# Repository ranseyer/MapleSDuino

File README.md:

View this project on [CADLAB.io](https://cadlab.io/project/2431). 

# MapleSDuino
 Signalduino Hardware based on a Maple-Mini

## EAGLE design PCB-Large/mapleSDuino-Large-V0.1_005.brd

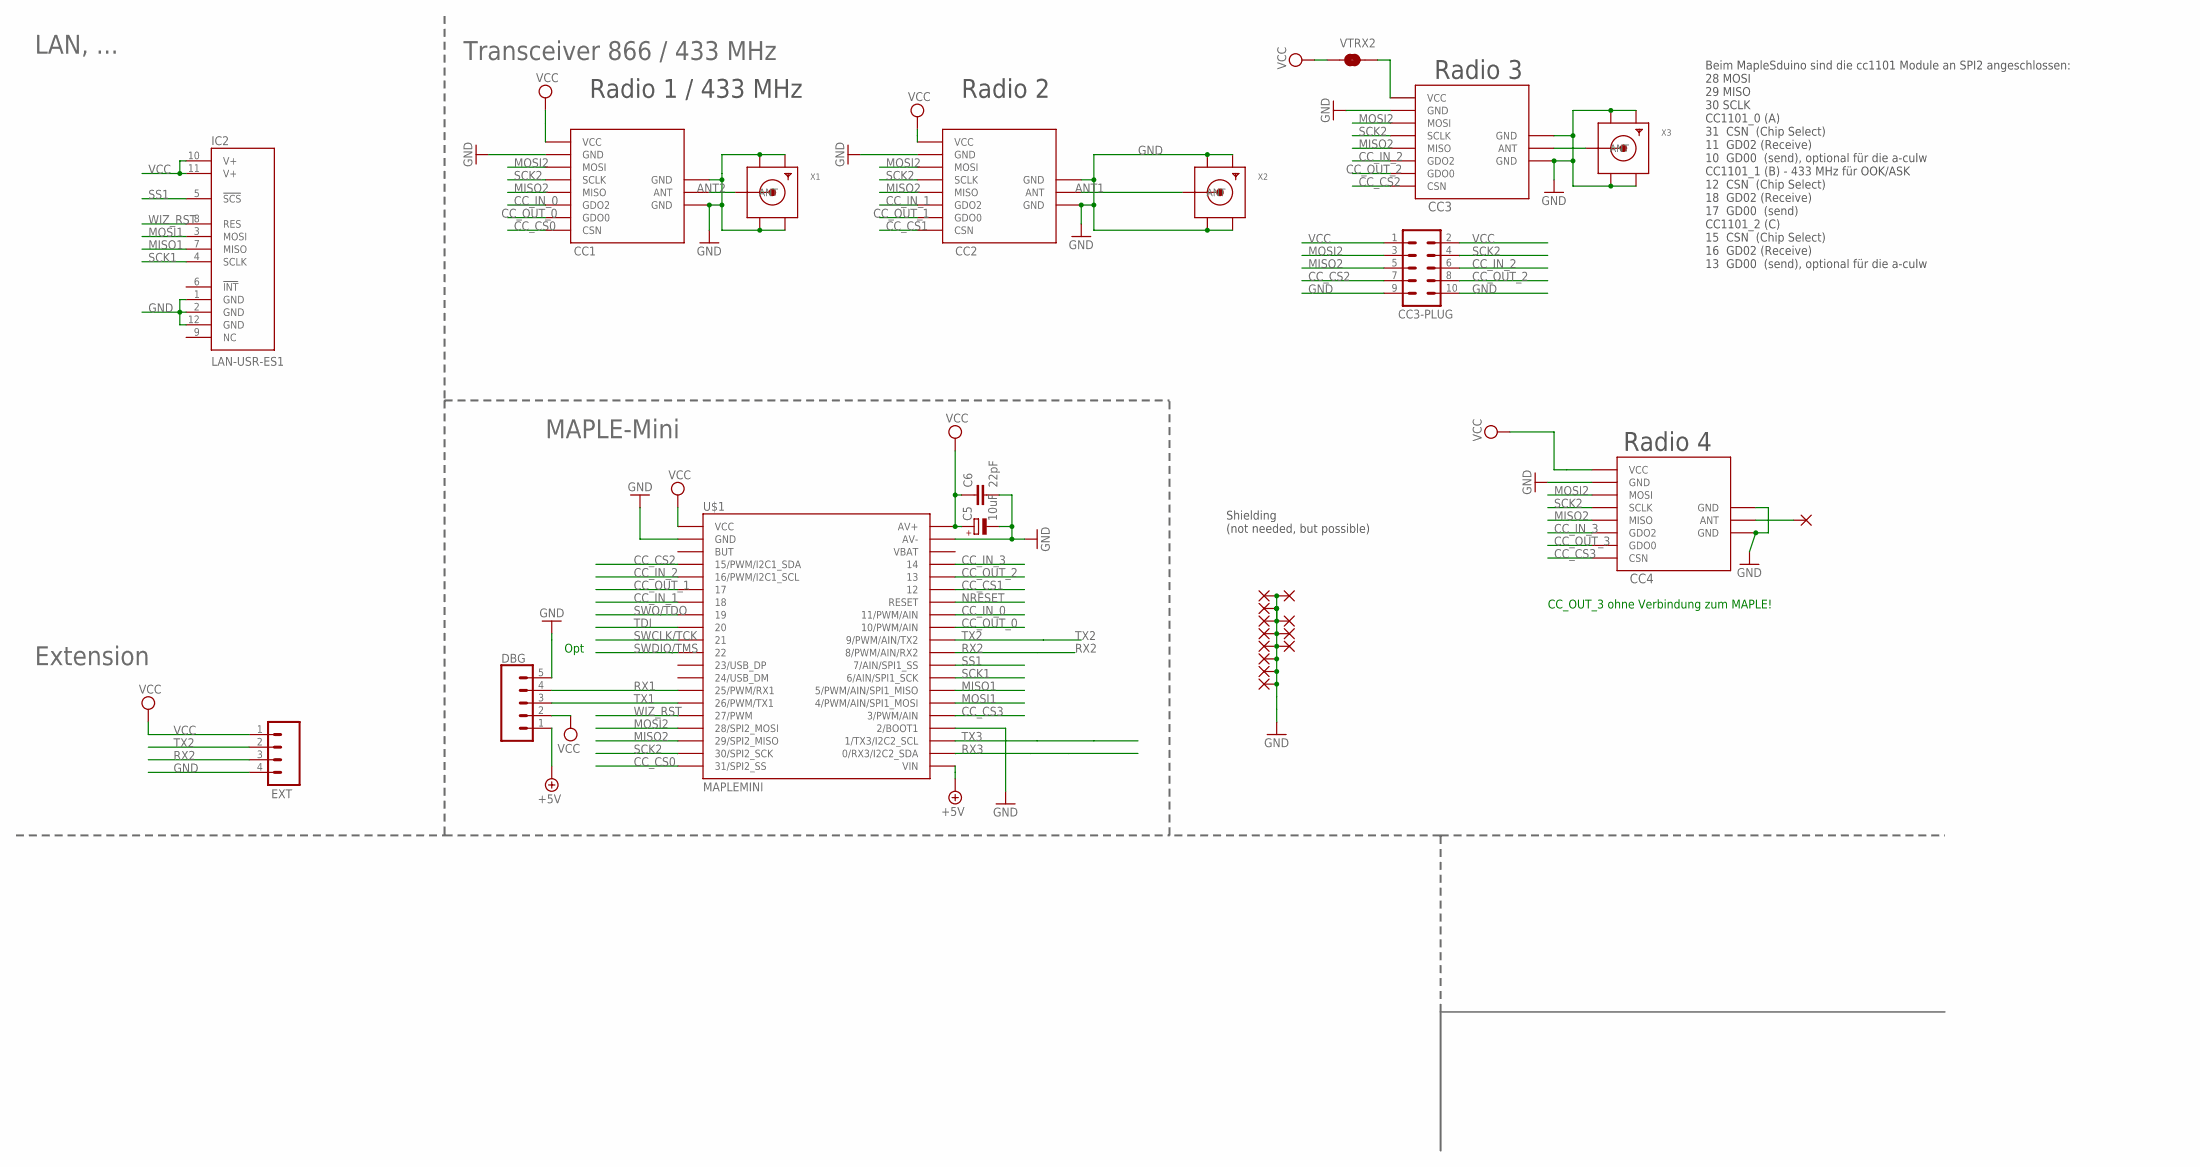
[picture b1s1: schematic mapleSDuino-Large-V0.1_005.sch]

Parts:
C5: 10uF; R/2012-12W
C6: 22pF; C0805
CC1: CC1101; CC1101_MODULE1_SMD
CC2, CC3, CC4: CC1101_MODULE1SMD; CC1101_MODULE1_SMD
CC3-PLUG: MA05-2
DBG: CONN_05LOCK; 1X05_LOCK
EXT: CONN_04PTH; 1X04
IC2: LAN-USR-ES1; USR-ES1
PAD1, PAD2, PAD3, PAD4, PAD5, PAD6, PAD7, PAD8, PAD9, PAD10, PAD11, PAD12, PAD13: WIREPADSMD1,27-254; SMD1,27-2,54
U$1: MAPLEMINI; 20-DIP
VTRX2: JUMPER-SMT_2_NC_TRACE_SILK; SMT-JUMPER_2_NC_TRACE_SILK
X1, X2, X3: SMACONNECTOR_EDGE; SMA_EDGELAUNCH

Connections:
+5V: DBG.1, U$1.21 (VIN)
ANT1: CC2.ANT, X2.P (ANT)
ANT2: CC1.ANT, X1.P (ANT)
ANT3: CC3.ANT, X3.P (ANT)
CC_CS0: CC1.CSN, U$1.20 (31/SPI2_SS)
CC_CS1: CC2.CSN, U$1.35 (12)
CC_CS2: CC3.CSN, CC3-PLUG.7, U$1.4 (15/PWM/I2C1_SDA)
CC_CS3: CC4.CSN, U$1.25 (3/PWM/AIN)
CC_IN_0: CC1.GDO2, U$1.33 (11/PWM/AIN)
CC_IN_1: CC2.GDO2, U$1.7 (18)
CC_IN_2: CC3.GDO2, CC3-PLUG.6, U$1.5 (16/PWM/I2C1_SCL)
CC_IN_3: CC4.GDO2, U$1.37 (14)
CC_OUT_0: CC1.GDO0, U$1.32 (10/PWM/AIN)
CC_OUT_1: CC2.GDO0, U$1.6 (17)
CC_OUT_2: CC3.GDO0, CC3-PLUG.8, U$1.36 (13)
CC_OUT_3: CC4.GDO0
GND: C5.-, C6.2, CC1.GND@0 (GND), CC1.GND@1 (GND), CC1.GND@2 (GND), CC2.GND@0 (GND), CC2.GND@1 (GND), CC2.GND@2 (GND), CC3.GND@0 (GND), CC3.GND@1 (GND), CC3.GND@2 (GND), CC3-PLUG.9, CC3-PLUG.10, CC4.GND@0 (GND), CC4.GND@1 (GND), CC4.GND@2 (GND), DBG.5, EXT.4, IC2.1 (GND), IC2.2 (GND), IC2.12 (GND), PAD1.1, PAD2.1, PAD3.1, PAD4.1, PAD5.1, PAD6.1, PAD7.1, PAD8.1, PAD9.1, PAD10.1, PAD11.1, PAD12.1, U$1.2 (GND), U$1.24 (2/BOOT1), U$1.39 (AV-), X1.GND@1 (GND4), X1.GND@2 (GND3), X1.GND@3 (GND2), X1.GND@4 (GND1), X2.GND@1 (GND4), X2.GND@2 (GND3), X2.GND@3 (GND2), X2.GND@4 (GND1), X3.GND@1 (GND4), X3.GND@2 (GND3), X3.GND@3 (GND2), X3.GND@4 (GND1)
MISO1: IC2.7 (MISO), U$1.27 (5/PWM/AIN/SPI1_MISO)
MISO2: CC1.MISO, CC2.MISO, CC3.MISO, CC3-PLUG.5, CC4.MISO, U$1.18 (29/SPI2_MISO)
MOSI1: IC2.3 (MOSI), U$1.26 (4/PWM/AIN/SPI1_MOSI)
MOSI2: CC1.MOSI, CC2.MOSI, CC3.MOSI, CC3-PLUG.3, CC4.MOSI, U$1.17 (28/SPI2_MOSI)
unnamed: CC3.VCC, VTRX2.2
unnamed: CC4.ANT, PAD13.1
NRESET: U$1.34 (RESET)
RX1: DBG.4, U$1.14 (25/PWM/RX1)
RX2: EXT.3, U$1.30 (8/PWM/AIN/RX2)
RX3: U$1.22 (0/RX3/I2C2_SDA)
SCK1: IC2.4 (SCLK), U$1.28 (6/AIN/SPI1_SCK)
SCK2: CC1.SCLK, CC2.SCLK, CC3.SCLK, CC3-PLUG.4, CC4.SCLK, U$1.19 (30/SPI2_SCK)
SS1: IC2.5 (!SCS!), U$1.29 (7/AIN/SPI1_SS)
SWCLK/TCK: U$1.10 (21)
SWDIO/TMS: U$1.11 (22)
SWO/TDO: U$1.8 (19)
TDI: U$1.9 (20)
TX1: DBG.3, U$1.15 (26/PWM/TX1)
TX2: EXT.2, U$1.31 (9/PWM/AIN/TX2)
TX3: U$1.23 (1/TX3/I2C2_SCL)
VCC: C5.+, C6.1, CC1.VCC, CC2.VCC, CC3-PLUG.1, CC3-PLUG.2, CC4.VCC, DBG.2, EXT.1, IC2.10 (V+), IC2.11 (V+), U$1.1 (VCC), U$1.40 (AV+), VTRX2.1
WIZ_RST: IC2.8 (RES), U$1.16 (27/PWM)

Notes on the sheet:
Radio 2
Radio 1 / 433 MHz
Opt
Extension
MAPLE-Mini
Transceiver 866 / 433 MHz
LAN, ...
Radio 3
Shielding (not needed, but possible)
Radio 4
CC_OUT_3 ohne Verbindung zum MAPLE!
Beim MapleSduino sind die cc1101 Module an SPI2 angeschlossen: 28 MOSI 29 MISO 30 SCLK CC1101_0 (A) 31 CSN (Chip Select) 11 GD02 (Receive) 10 GD00 (send), optional für die a-culw CC1101_1 (B) - 433 MHz für OOK/ASK 12 CSN (Chip Select) 18 GD02 (Receive) 17 GD00 (send) CC1101_2 (C) 15 CSN (Chip Selec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

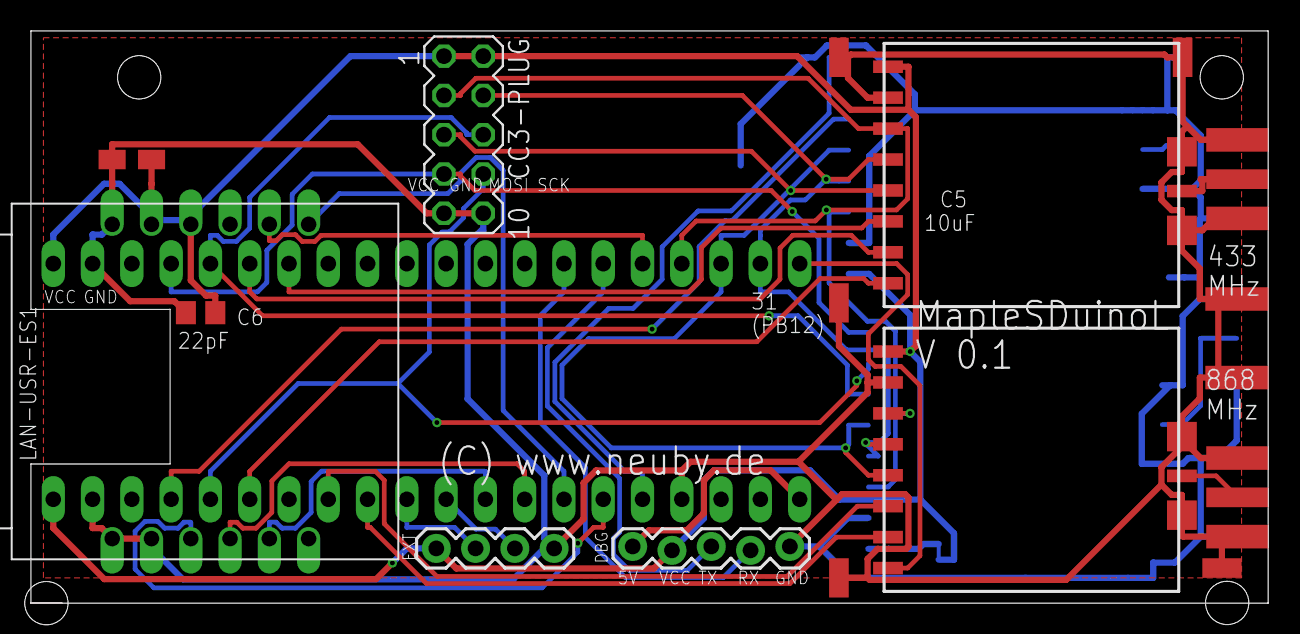
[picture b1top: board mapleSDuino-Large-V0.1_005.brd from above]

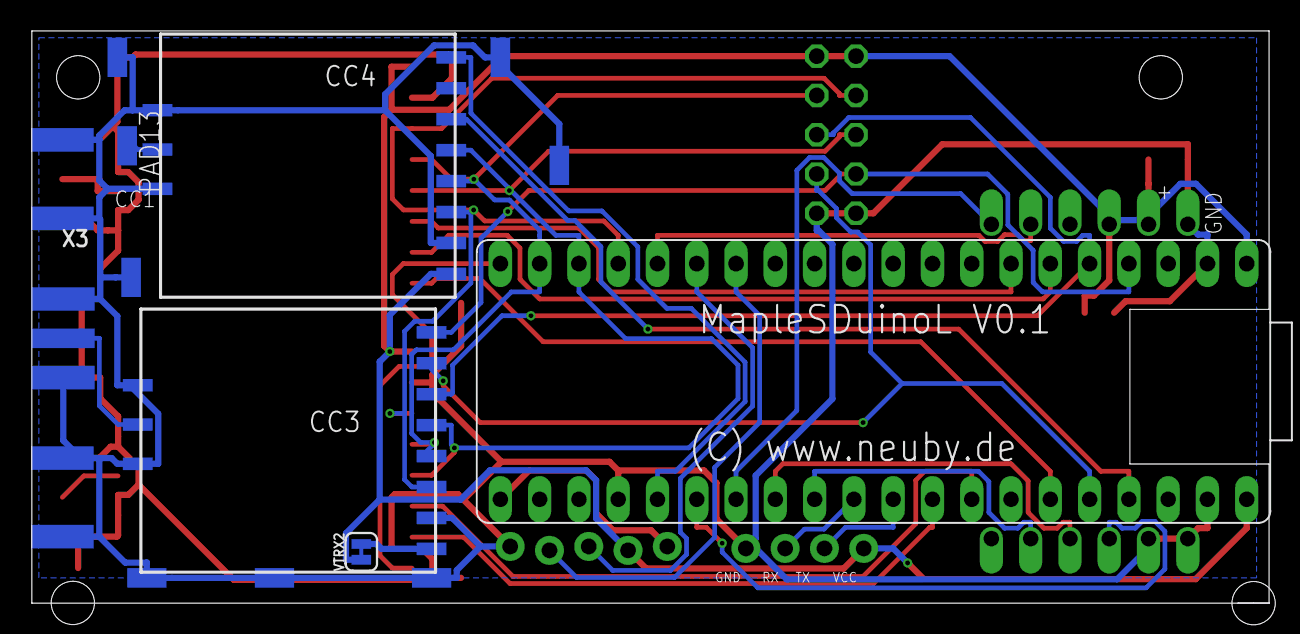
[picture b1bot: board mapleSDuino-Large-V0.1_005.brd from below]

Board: 2 copper layers, 80.0 x 37.0 mm, 28 parts (13 on the bottom side), 31 nets.

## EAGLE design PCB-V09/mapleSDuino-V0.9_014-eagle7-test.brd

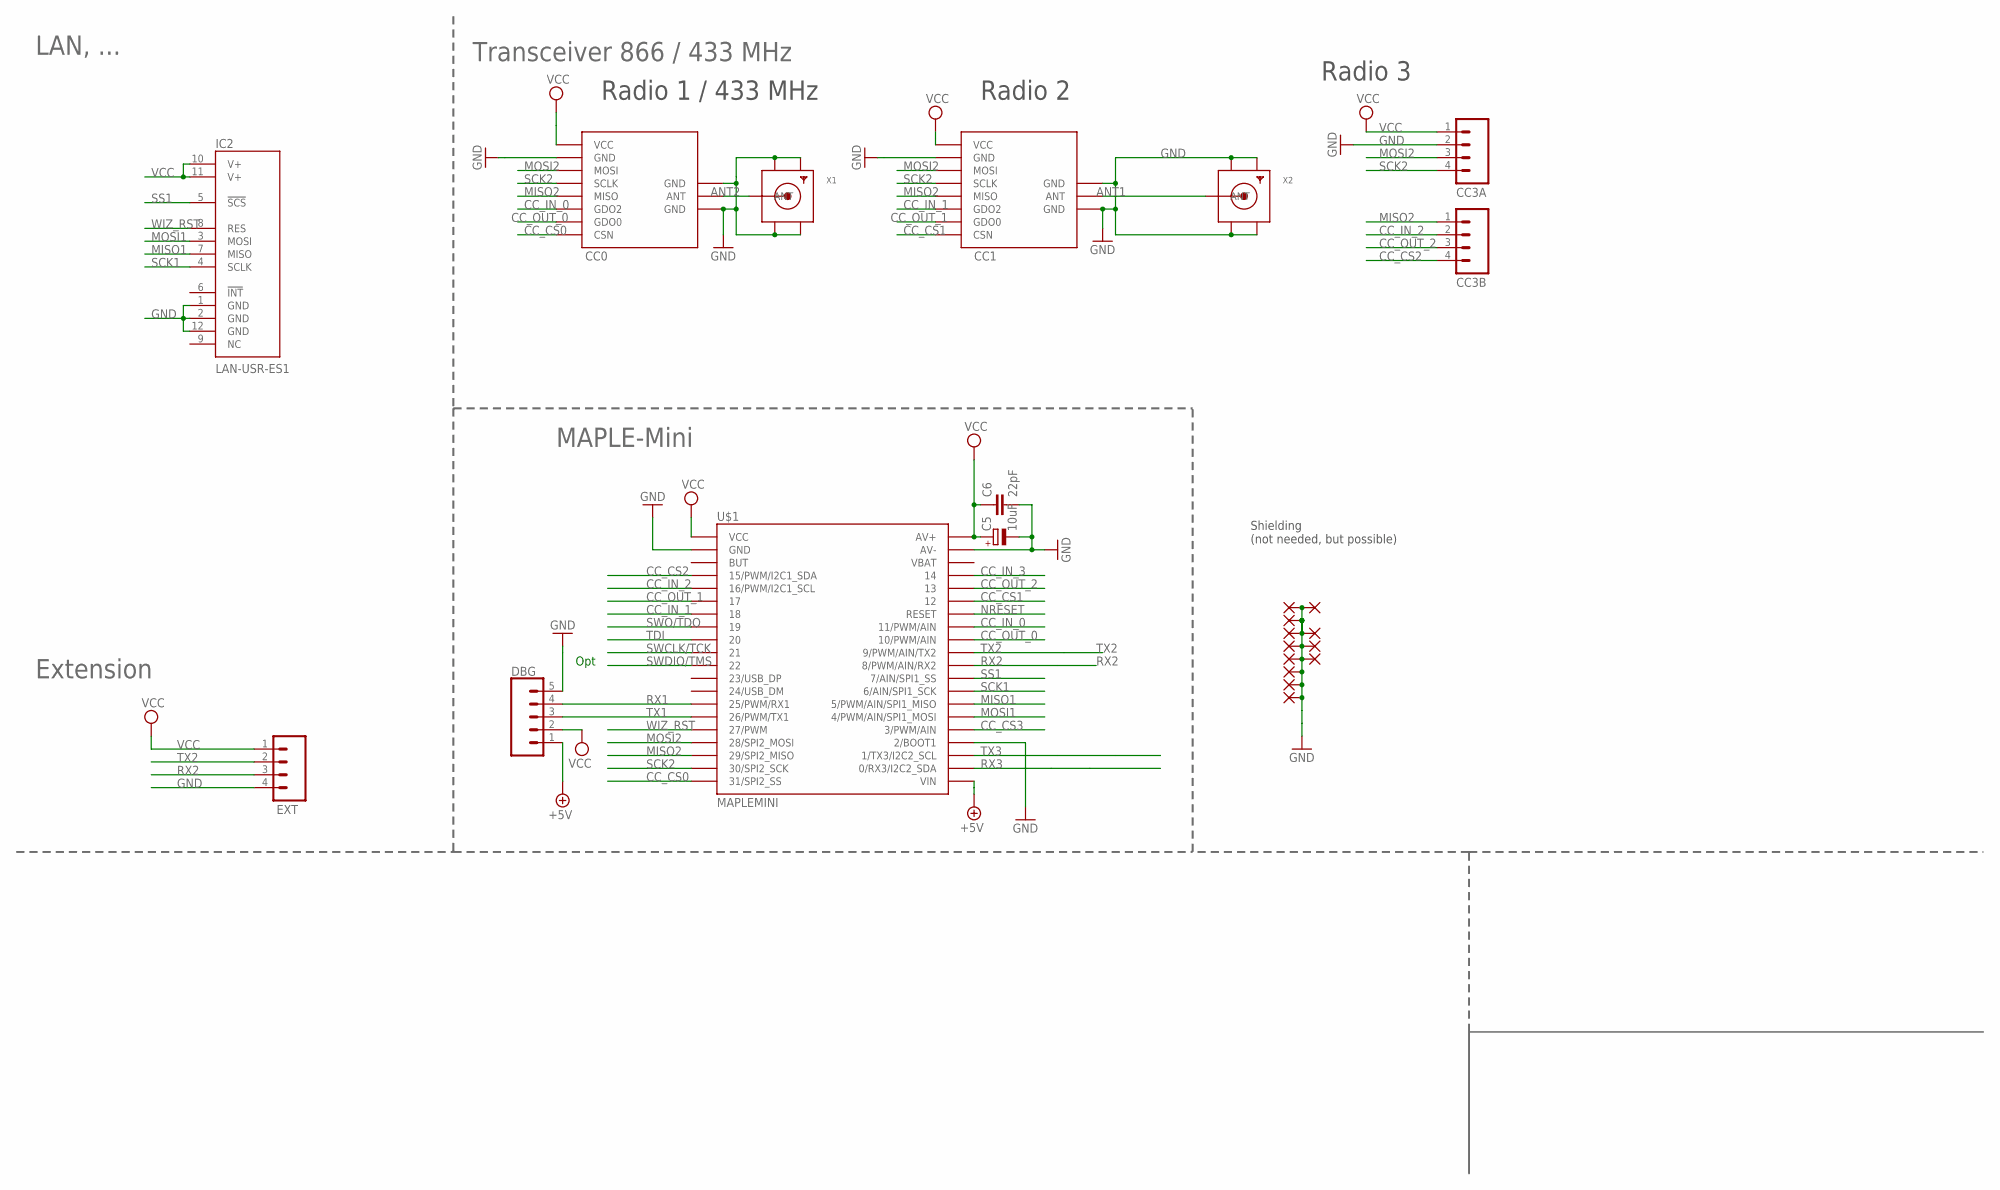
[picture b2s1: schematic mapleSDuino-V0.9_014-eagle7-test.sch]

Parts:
C5: 10uF; R/2012-12W
C6: 22pF; C0805
CC0: CC1101; CC1101_MODULE1_SMD
CC1: CC1101_MODULE1SMD; CC1101_MODULE1_SMD
CC3A, CC3B: CONN_04PTH; 1X04
DBG: CONN_05LOCK; 1X05_LOCK
EXT: CONN_04PTH; 1X04
IC2: LAN-USR-ES1; USR-ES1
PAD1, PAD2, PAD3, PAD4, PAD5, PAD6, PAD7, PAD8, PAD9, PAD10, PAD11, PAD12: WIREPADSMD1,27-254; SMD1,27-2,54
U$1: MAPLEMINI; 20-DIP
X1, X2: SMACONNECTOR_EDGE; SMA_EDGELAUNCH

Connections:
+5V: DBG.1, U$1.21 (VIN)
ANT1: CC1.ANT, X2.P (ANT)
ANT2: CC0.ANT, X1.P (ANT)
CC_CS0: CC0.CSN, U$1.20 (31/SPI2_SS)
CC_CS1: CC1.CSN, U$1.35 (12)
CC_CS2: CC3B.4, U$1.4 (15/PWM/I2C1_SDA)
CC_CS3: U$1.25 (3/PWM/AIN)
CC_IN_0: CC0.GDO2, U$1.33 (11/PWM/AIN)
CC_IN_1: CC1.GDO2, U$1.7 (18)
CC_IN_2: CC3B.2, U$1.5 (16/PWM/I2C1_SCL)
CC_IN_3: U$1.37 (14)
CC_OUT_0: CC0.GDO0, U$1.32 (10/PWM/AIN)
CC_OUT_1: CC1.GDO0, U$1.6 (17)
CC_OUT_2: CC3B.3, U$1.36 (13)
GND: C5.-, C6.2, CC0.GND@0 (GND), CC0.GND@1 (GND), CC0.GND@2 (GND), CC1.GND@0 (GND), CC1.GND@1 (GND), CC1.GND@2 (GND), CC3A.2, DBG.5, EXT.4, IC2.1 (GND), IC2.2 (GND), IC2.12 (GND), PAD1.1, PAD2.1, PAD3.1, PAD4.1, PAD5.1, PAD6.1, PAD7.1, PAD8.1, PAD9.1, PAD10.1, PAD11.1, PAD12.1, U$1.2 (GND), U$1.24 (2/BOOT1), U$1.39 (AV-), X1.GND@1 (GND4), X1.GND@2 (GND3), X1.GND@3 (GND2), X1.GND@4 (GND1), X2.GND@1 (GND4), X2.GND@2 (GND3), X2.GND@3 (GND2), X2.GND@4 (GND1)
MISO1: IC2.7 (MISO), U$1.27 (5/PWM/AIN/SPI1_MISO)
MISO2: CC0.MISO, CC1.MISO, CC3B.1, U$1.18 (29/SPI2_MISO)
MOSI1: IC2.3 (MOSI), U$1.26 (4/PWM/AIN/SPI1_MOSI)
MOSI2: CC0.MOSI, CC1.MOSI, CC3A.3, U$1.17 (28/SPI2_MOSI)
NRESET: U$1.34 (RESET)
RX1: DBG.4, U$1.14 (25/PWM/RX1)
RX2: EXT.3, U$1.30 (8/PWM/AIN/RX2)
RX3: U$1.22 (0/RX3/I2C2_SDA)
SCK1: IC2.4 (SCLK), U$1.28 (6/AIN/SPI1_SCK)
SCK2: CC0.SCLK, CC1.SCLK, CC3A.4, U$1.19 (30/SPI2_SCK)
SS1: IC2.5 (!SCS!), U$1.29 (7/AIN/SPI1_SS)
SWCLK/TCK: U$1.10 (21)
SWDIO/TMS: U$1.11 (22)
SWO/TDO: U$1.8 (19)
TDI: U$1.9 (20)
TX1: DBG.3, U$1.15 (26/PWM/TX1)
TX2: EXT.2, U$1.31 (9/PWM/AIN/TX2)
TX3: U$1.23 (1/TX3/I2C2_SCL)
VCC: C5.+, C6.1, CC0.VCC, CC1.VCC, CC3A.1, DBG.2, EXT.1, IC2.10 (V+), IC2.11 (V+), U$1.1 (VCC), U$1.40 (AV+)
WIZ_RST: IC2.8 (RES), U$1.16 (27/PWM)

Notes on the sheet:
Radio 2
Radio 1 / 433 MHz
Opt
Extension
MAPLE-Mini
Transceiver 866 / 433 MHz
LAN, ...
Radio 3
Shielding (not needed, but possible)

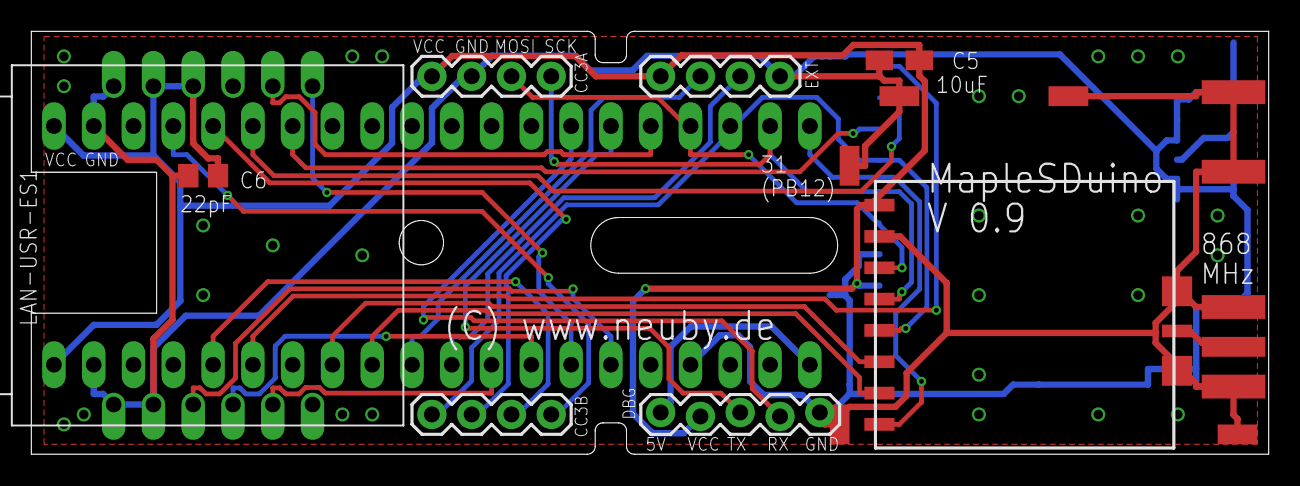
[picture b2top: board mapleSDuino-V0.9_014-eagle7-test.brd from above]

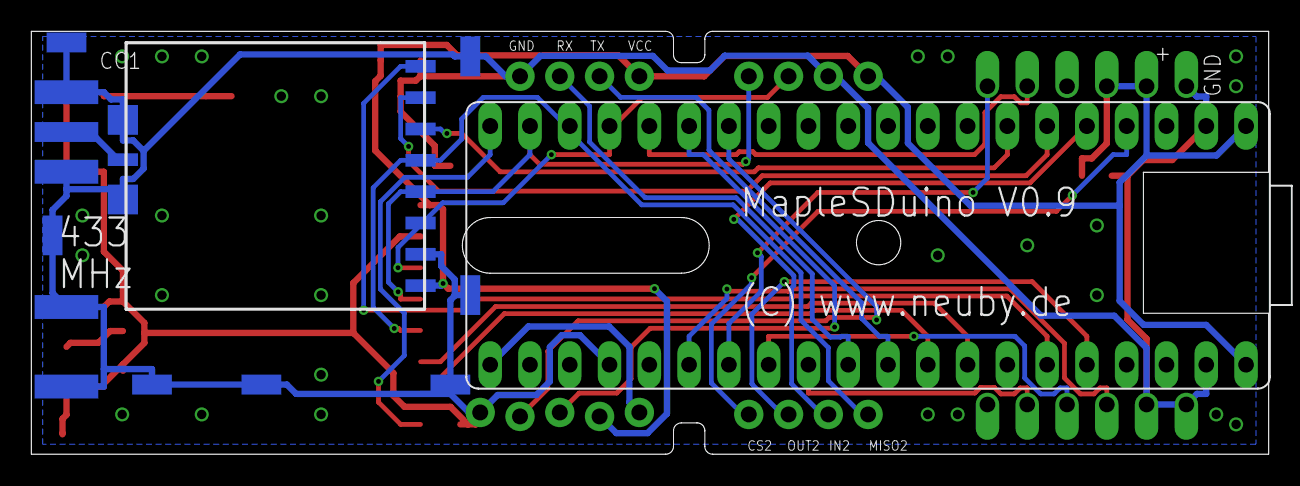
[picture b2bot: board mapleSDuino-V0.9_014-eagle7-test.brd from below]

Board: 2 copper layers, 79.0 x 27.0 mm, 24 parts (10 on the bottom side), 26 nets.

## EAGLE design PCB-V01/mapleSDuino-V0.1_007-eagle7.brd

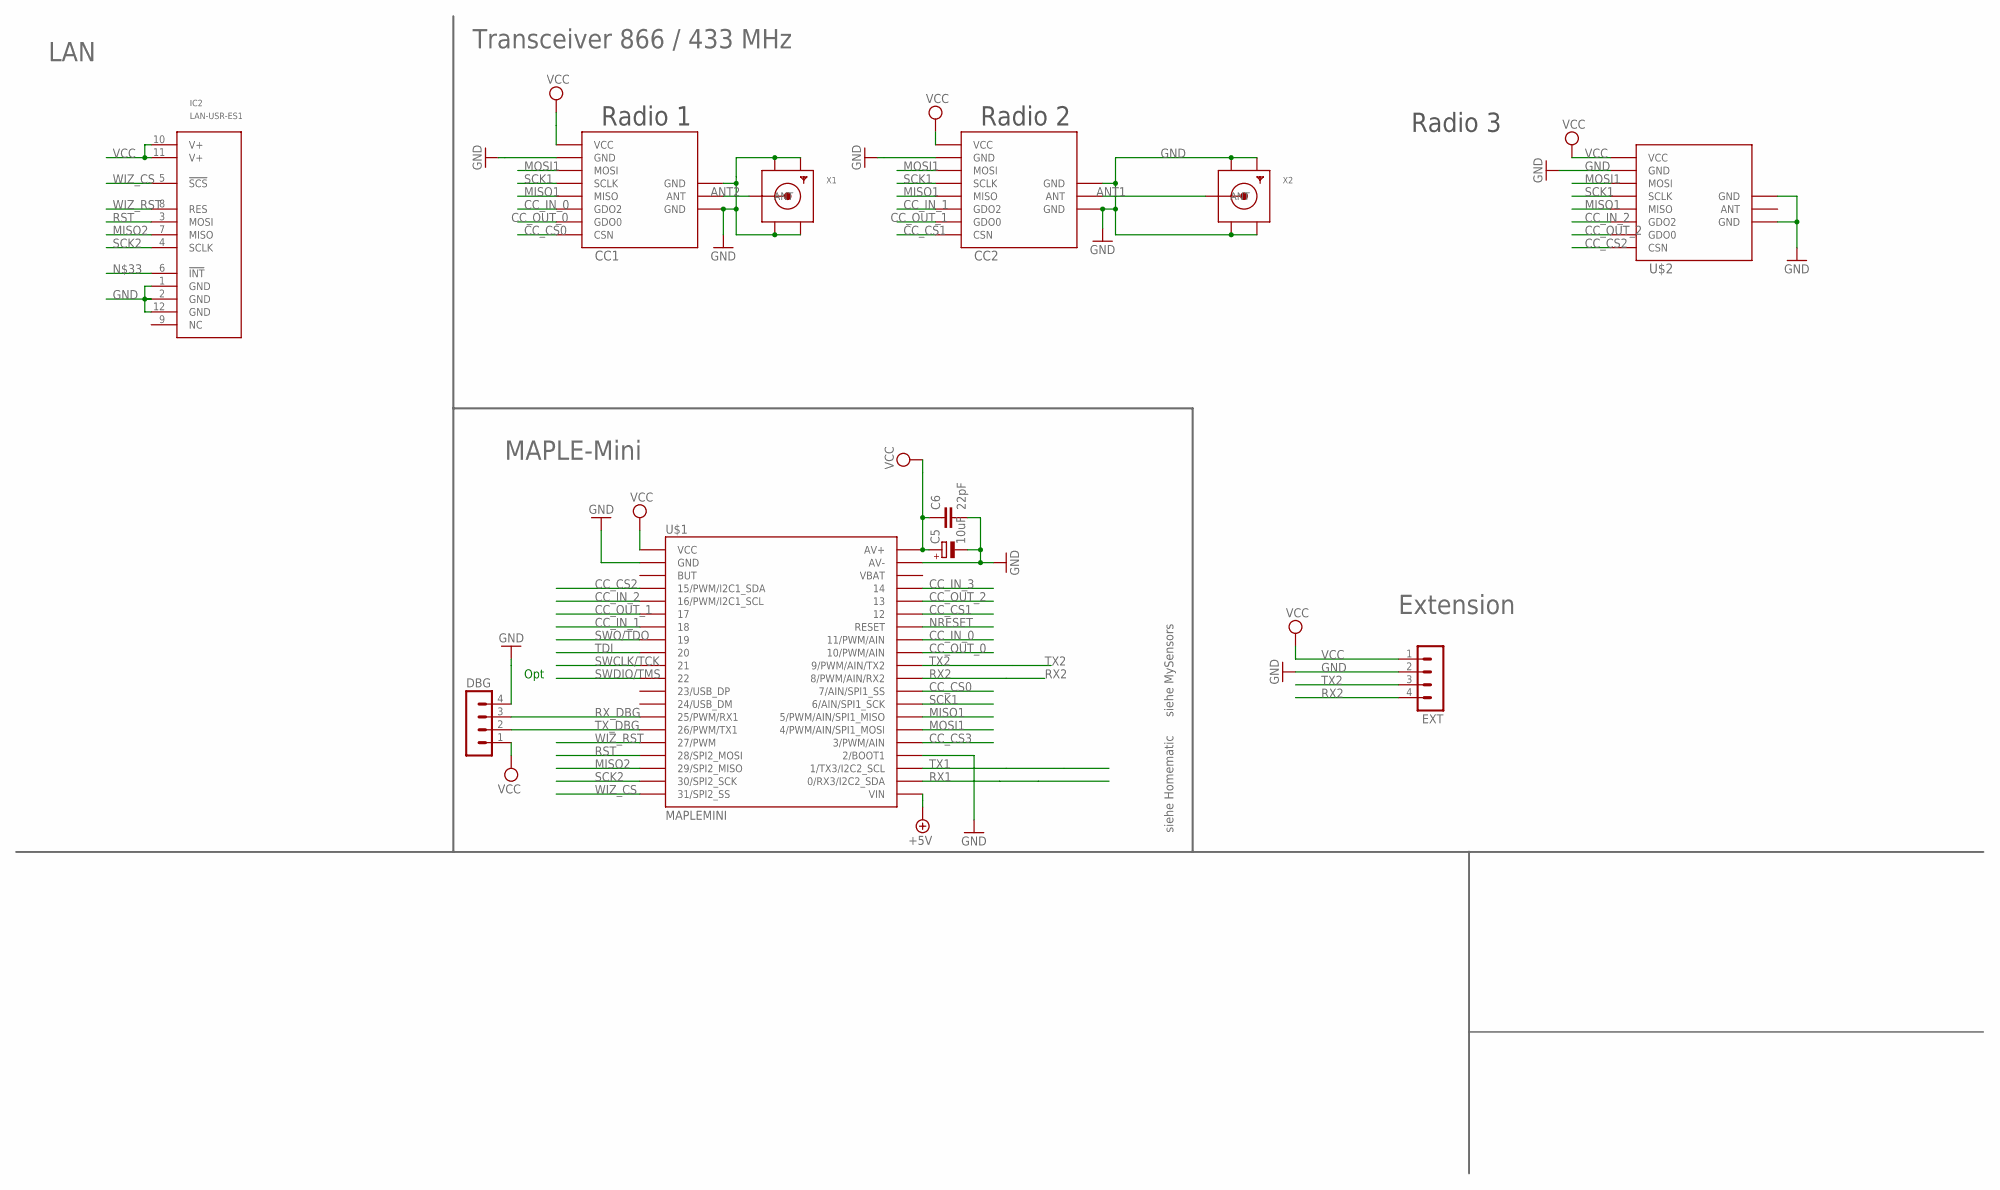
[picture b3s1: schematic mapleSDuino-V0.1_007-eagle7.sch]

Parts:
C5: 10uF; R/2012-12W
C6: 22pF; C0805
CC1: CC1101; CC1101_MODULE1_SMD
CC2: CC1101_MODULE1SMD; CC1101_MODULE1_SMD
DBG: MA04-1
EXT: MA04-1
IC2: LAN-USR-ES1; USR-ES1
U$1: MAPLEMINI; 20-DIP
U$2: CC1101_MODULE1DIL_BIG; CC1101_MODULE1_DIL-2
X1, X2: SMACONNECTOR_EDGE; SMA_EDGELAUNCH

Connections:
+5V: U$1.21 (VIN)
ANT1: CC2.ANT, X2.P (ANT)
ANT2: CC1.ANT, X1.P (ANT)
CC_CS0: CC1.CSN, U$1.29 (7/AIN/SPI1_SS)
CC_CS1: CC2.CSN, U$1.35 (12)
CC_CS2: U$1.4 (15/PWM/I2C1_SDA), U$2.8 (CSN)
CC_CS3: U$1.25 (3/PWM/AIN)
CC_IN_0: CC1.GDO2, U$1.33 (11/PWM/AIN)
CC_IN_1: CC2.GDO2, U$1.7 (18)
CC_IN_2: U$1.5 (16/PWM/I2C1_SCL), U$2.6 (GDO2)
CC_IN_3: U$1.37 (14)
CC_OUT_0: CC1.GDO0, U$1.32 (10/PWM/AIN)
CC_OUT_1: CC2.GDO0, U$1.6 (17)
CC_OUT_2: U$1.36 (13), U$2.7 (GDO0)
GND: C5.-, C6.2, CC1.GND@0 (GND), CC1.GND@1 (GND), CC1.GND@2 (GND), CC2.GND@0 (GND), CC2.GND@1 (GND), CC2.GND@2 (GND), DBG.4, EXT.2, IC2.1 (GND), IC2.2 (GND), IC2.12 (GND), U$1.2 (GND), U$1.24 (2/BOOT1), U$1.39 (AV-), U$2.2 (GND), U$2.9 (GND), U$2.11 (GND), X1.GND@1 (GND4), X1.GND@2 (GND3), X1.GND@3 (GND2), X1.GND@4 (GND1), X2.GND@1 (GND4), X2.GND@2 (GND3), X2.GND@3 (GND2), X2.GND@4 (GND1)
MISO1: CC1.MISO, CC2.MISO, U$1.27 (5/PWM/AIN/SPI1_MISO), U$2.5 (MISO)
MISO2: IC2.7 (MISO), U$1.18 (29/SPI2_MISO)
MOSI1: CC1.MOSI, CC2.MOSI, U$1.26 (4/PWM/AIN/SPI1_MOSI), U$2.3 (MOSI)
NRESET: U$1.34 (RESET)
RST: IC2.3 (MOSI), U$1.17 (28/SPI2_MOSI)
RX1: U$1.22 (0/RX3/I2C2_SDA)
RX2: EXT.4, U$1.30 (8/PWM/AIN/RX2)
RX_DBG: DBG.3, U$1.14 (25/PWM/RX1)
SCK1: CC1.SCLK, CC2.SCLK, U$1.28 (6/AIN/SPI1_SCK), U$2.4 (SCLK)
SCK2: IC2.4 (SCLK), U$1.19 (30/SPI2_SCK)
SWCLK/TCK: U$1.10 (21)
SWDIO/TMS: U$1.11 (22)
SWO/TDO: U$1.8 (19)
TDI: U$1.9 (20)
TX1: U$1.23 (1/TX3/I2C2_SCL)
TX2: EXT.3, U$1.31 (9/PWM/AIN/TX2)
TX_DBG: DBG.2, U$1.15 (26/PWM/TX1)
VCC: C5.+, C6.1, CC1.VCC, CC2.VCC, DBG.1, EXT.1, IC2.10 (V+), IC2.11 (V+), U$1.1 (VCC), U$1.40 (AV+), U$2.1 (VCC)
WIZ_CS: IC2.5 (!SCS!), U$1.20 (31/SPI2_SS)
WIZ_RST: IC2.8 (RES), U$1.16 (27/PWM)

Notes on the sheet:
Radio 2
Radio 1
Opt
siehe Homematic
siehe MySensors
Extension
MAPLE-Mini
Transceiver 866 / 433 MHz
LAN
Radio 3

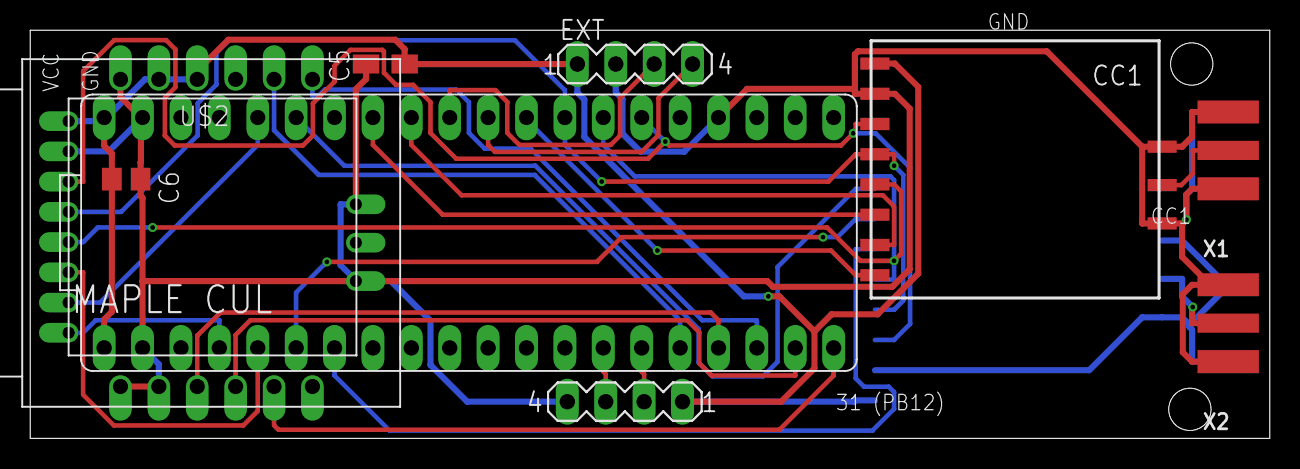
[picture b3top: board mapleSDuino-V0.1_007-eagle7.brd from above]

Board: 2 copper layers, 82.0 x 27.0 mm, 11 parts (1 on the bottom side), 25 nets.

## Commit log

2020-01-18 V010
2020-01-23 Update
    SPI + TRX Pins, Shielding, 5V Pin
2020-01-23 Backlink to CADLAB.io has been added.
2020-01-24 Fix CS
2020-01-24 pin 31
2020-01-28 files renamed, added information file, no changes to Eagle files (test if access works)
2020-01-28 Labels Part1
2020-02-06 small update: - cosmetics in schematic - cosmetics in layout - questions see FHEM forum
2020-02-07 LAN Module moved
2020-02-12 V01-final
2020-03-21 V0.2 / Photos
2020-04-05 V0.9
2020-04-06 Longer milling slot
2020-06-16 Large 1st try; v009 Schematic

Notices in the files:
parts and their libraries:
SparkFun-Connectors: Licensing: Creative Commons ShareAlike 4.0 International - https://creativecommons.org/licenses/by-sa/4.0
